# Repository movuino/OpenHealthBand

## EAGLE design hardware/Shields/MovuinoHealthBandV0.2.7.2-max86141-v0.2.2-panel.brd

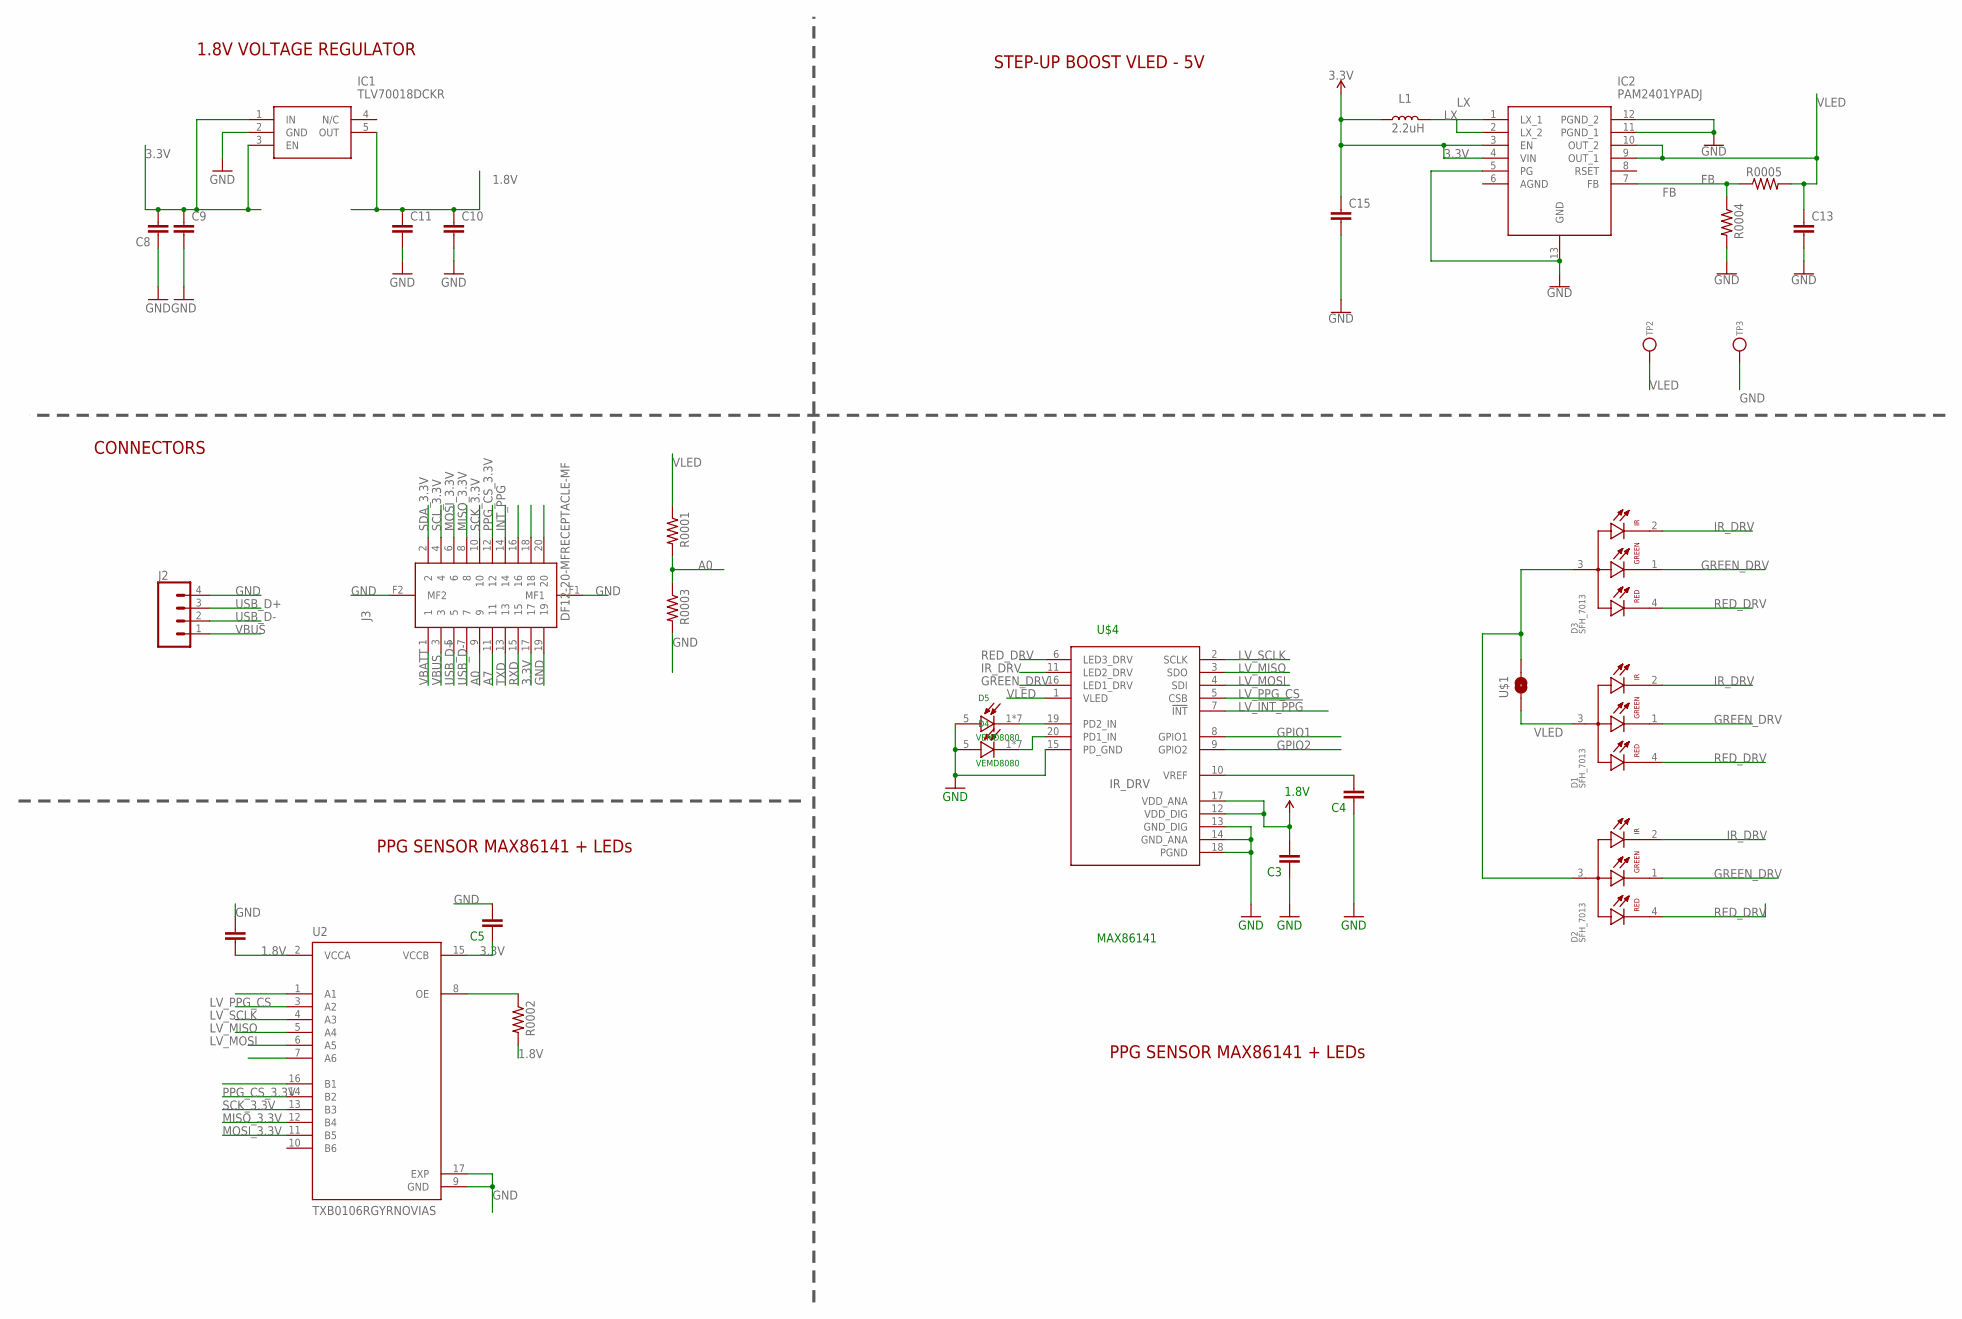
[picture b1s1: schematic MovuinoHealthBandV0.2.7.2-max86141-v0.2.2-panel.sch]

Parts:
C3: 1uF; 0402-CAP
C4: 10uF; 0402-CAP
C5, C6: 0.1uF; 0402-CAP
C8, C15: 10uF; 0402-CAP-SMALL-TDOCU
C9, C10: 0.1uF; 0402-CAP-SMALL-TDOCU
C11: 4.7uF; 0402-CAP-SMALL-TDOCU
C13: 22uF; 0402-CAP-SMALL-TDOCU
D1, D2, D3: SFH_7013
D4, D5: VEMD8080; XDCR_VEMD8080
IC1: TLV70018DCKR; SOT65P210X110-5N
IC2: PAM2401YPADJ; SON45P295X295X60-13N
J2: CONN_04POGO-2.54; POGO_2.54_X4
J3: DF12-20-MFRECEPTACLE-MF; DF12-20-DS
L1: 2.2uH; INDC2016X100N
R0001, R0002, R0003, R0004: 100K; 0402-RES
R0005: 750K; 0402-RES
TP2, TP3: TESTPOINT1MM-ROUND-CREAM; TESTPOINT_ROUND_1MM-CREAM
U2: TXB0106RGYRNOVIAS; QFN50P400X350X100-17N-2
U$1: 0402-JUMPER
U$4: MAX86141; 20_PIN_WLP

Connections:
1.8V: C3.2, C6.1, C10.1, C11.1, IC1.5 (OUT), R0002.2, U2.2 (VCCA), U$4.12 (VDD_DIG), U$4.17 (VDD_ANA)
3.3V: C5.1, C8.2, C9.1, C15.1, IC1.1 (IN), IC1.3 (EN), IC2.3 (EN), IC2.4 (VIN), J3.17, L1.1, U2.15 (VCCB)
A0: J3.9, R0001.2, R0003.1
A7: J3.11
FB: IC2.7 (FB), R0004.1, R0005.1
GND: C3.1, C4.1, C5.2, C6.2, C8.1, C9.2, C10.2, C11.2, C13.2, C15.2, D4.5 (A), D5.5 (A), IC1.2 (GND), IC2.5 (PG), IC2.11 (PGND_1), IC2.12 (PGND_2), IC2.13 (GND), J2.4, J3.19, J3.F1 (MF1), J3.F2 (MF2), R0003.2, R0004.2, TP3.P$1, U2.9 (GND), U2.17 (EXP), U$4.13 (GND_DIG), U$4.14 (GND_ANA), U$4.15 (PD_GND), U$4.18 (PGND)
GPIO1: U$4.8 (GPIO1)
GPIO2: U$4.9 (GPIO2)
GREEN_DRV: D1.1 (CATHODE_EMITTER_2), D2.1 (CATHODE_EMITTER_2), D3.1 (CATHODE_EMITTER_2), U$4.16 (LED1_DRV)
INT_PPG: J3.14
IR_DRV: D1.2 (CATHODE_EMITTER_3), D2.2 (CATHODE_EMITTER_3), D3.2 (CATHODE_EMITTER_3), U$4.11 (LED2_DRV)
LV_!INT_PPG!: U$4.7 (!INT!)
LV_MISO: U2.5 (A4), U$4.3 (SDO)
LV_MOSI: U2.6 (A5), U$4.4 (SDI)
LV_PPG_CS: U2.3 (A2), U$4.5 (CSB)
LV_SCLK: U2.4 (A3), U$4.2 (SCLK)
LX: IC2.1 (LX_1), IC2.2 (LX_2), L1.2
MISO_3.3V: J3.8, U2.12 (B4)
MOSI_3.3V: J3.6, U2.11 (B5)
unnamed: R0002.1, U2.8 (OE)
unnamed: C4.2, U$4.10 (VREF)
unnamed: D5.1 (C), D5.2 (C), D5.3 (C), D5.4 (C), D5.6 (C), D5.7 (C), D5.8 (C), U$4.19 (PD2_IN)
unnamed: D4.1 (C), D4.2 (C), D4.3 (C), D4.4 (C), D4.6 (C), D4.7 (C), D4.8 (C), U$4.20 (PD1_IN)
unnamed: D2.3 (ANODE_EMITTER_1/2/3), D3.3 (ANODE_EMITTER_1/2/3), U$1.2
PPG_CS_3.3V: J3.12, U2.14 (B2)
RED_DRV: D1.4 (CATHODE_EMITTER_1), D2.4 (CATHODE_EMITTER_1), D3.4 (CATHODE_EMITTER_1), U$4.6 (LED3_DRV)
RXD: J3.15
SCK_3.3V: J3.10, U2.13 (B3)
SCL_3.3V: J3.4
SDA_3.3V: J3.2
TXD: J3.13
USB_D+: J2.3, J3.5
USB_D-: J2.2, J3.7
VBATT: J3.1
VBUS: J2.1, J3.3
VLED: C13.1, D1.3 (ANODE_EMITTER_1/2/3), IC2.9 (OUT_1), IC2.10 (OUT_2), R0001.1, R0005.2, TP2.P$1, U$1.1, U$4.1 (VLED)

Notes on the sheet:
PPG SENSOR MAX86141 + LEDs
STEP-UP BOOST VLED - 5V
1.8V VOLTAGE REGULATOR
CONNECTORS

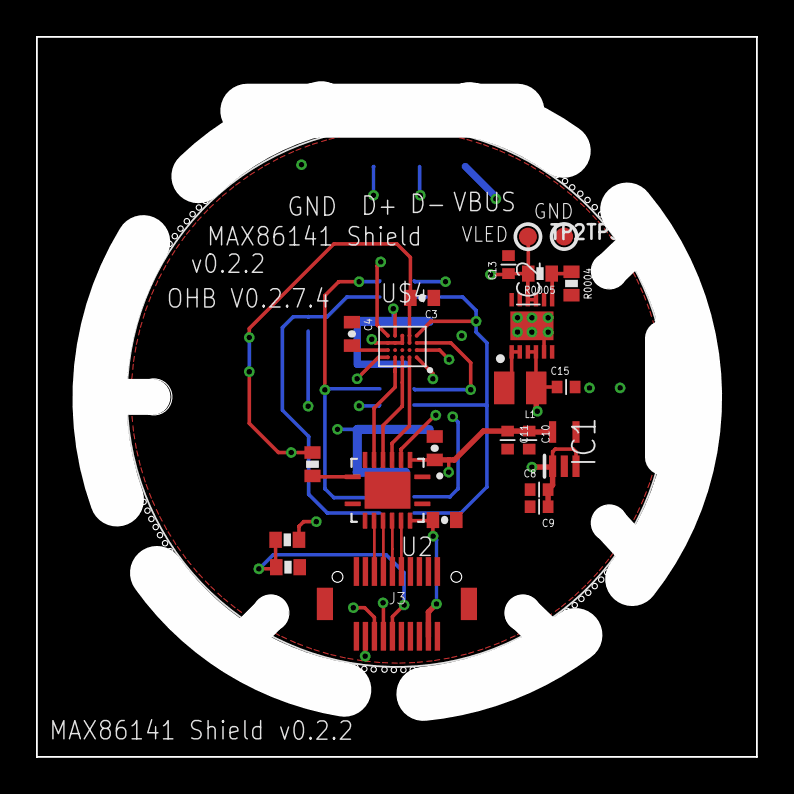
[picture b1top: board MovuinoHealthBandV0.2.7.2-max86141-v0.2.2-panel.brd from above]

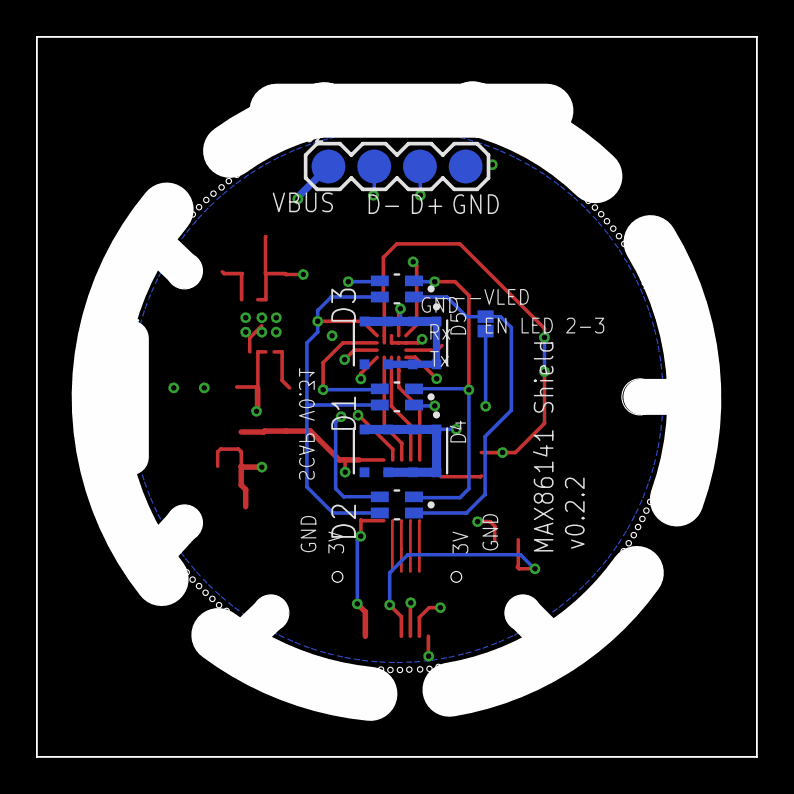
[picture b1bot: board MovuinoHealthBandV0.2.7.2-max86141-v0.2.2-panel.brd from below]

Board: 4 copper layers, 40.0 x 40.0 mm, 30 parts (7 on the bottom side), 26 nets.

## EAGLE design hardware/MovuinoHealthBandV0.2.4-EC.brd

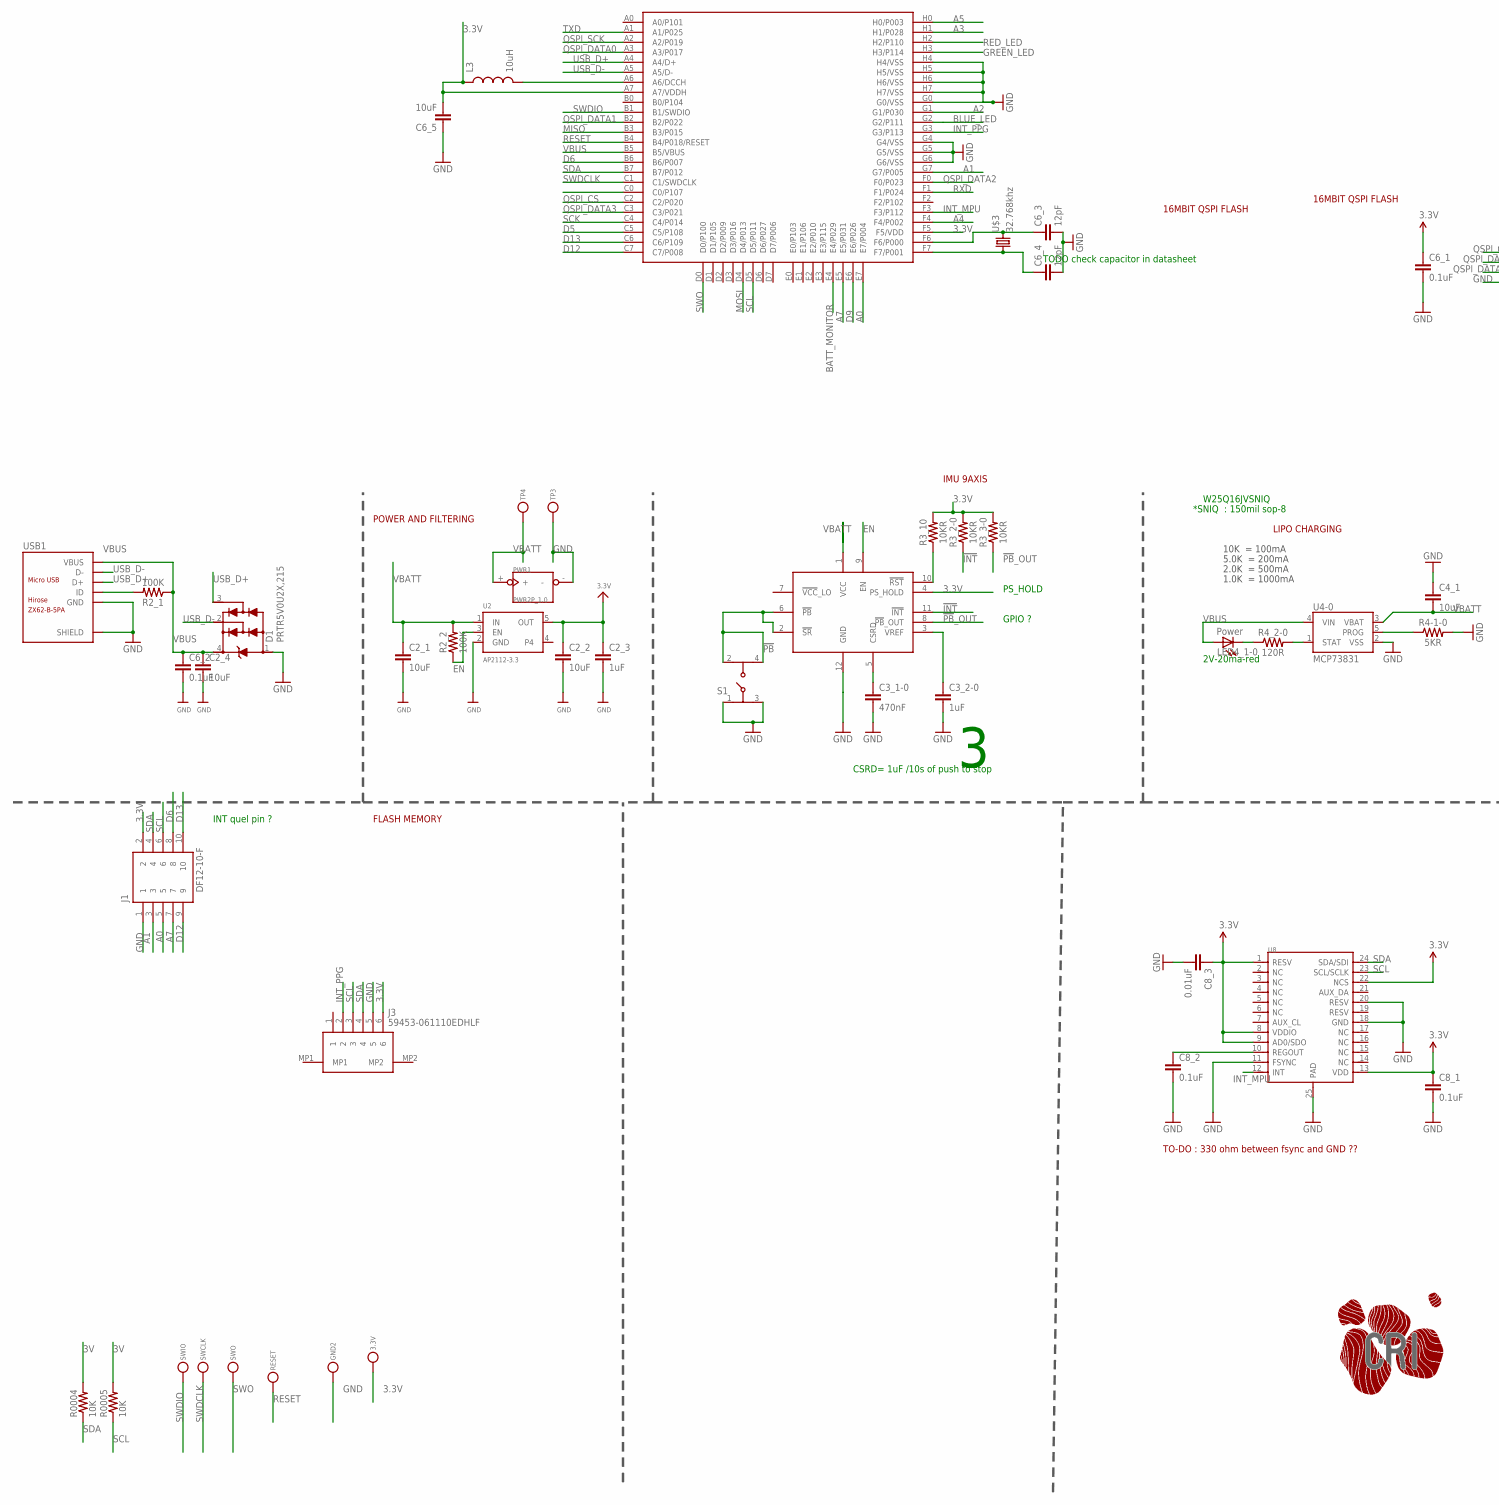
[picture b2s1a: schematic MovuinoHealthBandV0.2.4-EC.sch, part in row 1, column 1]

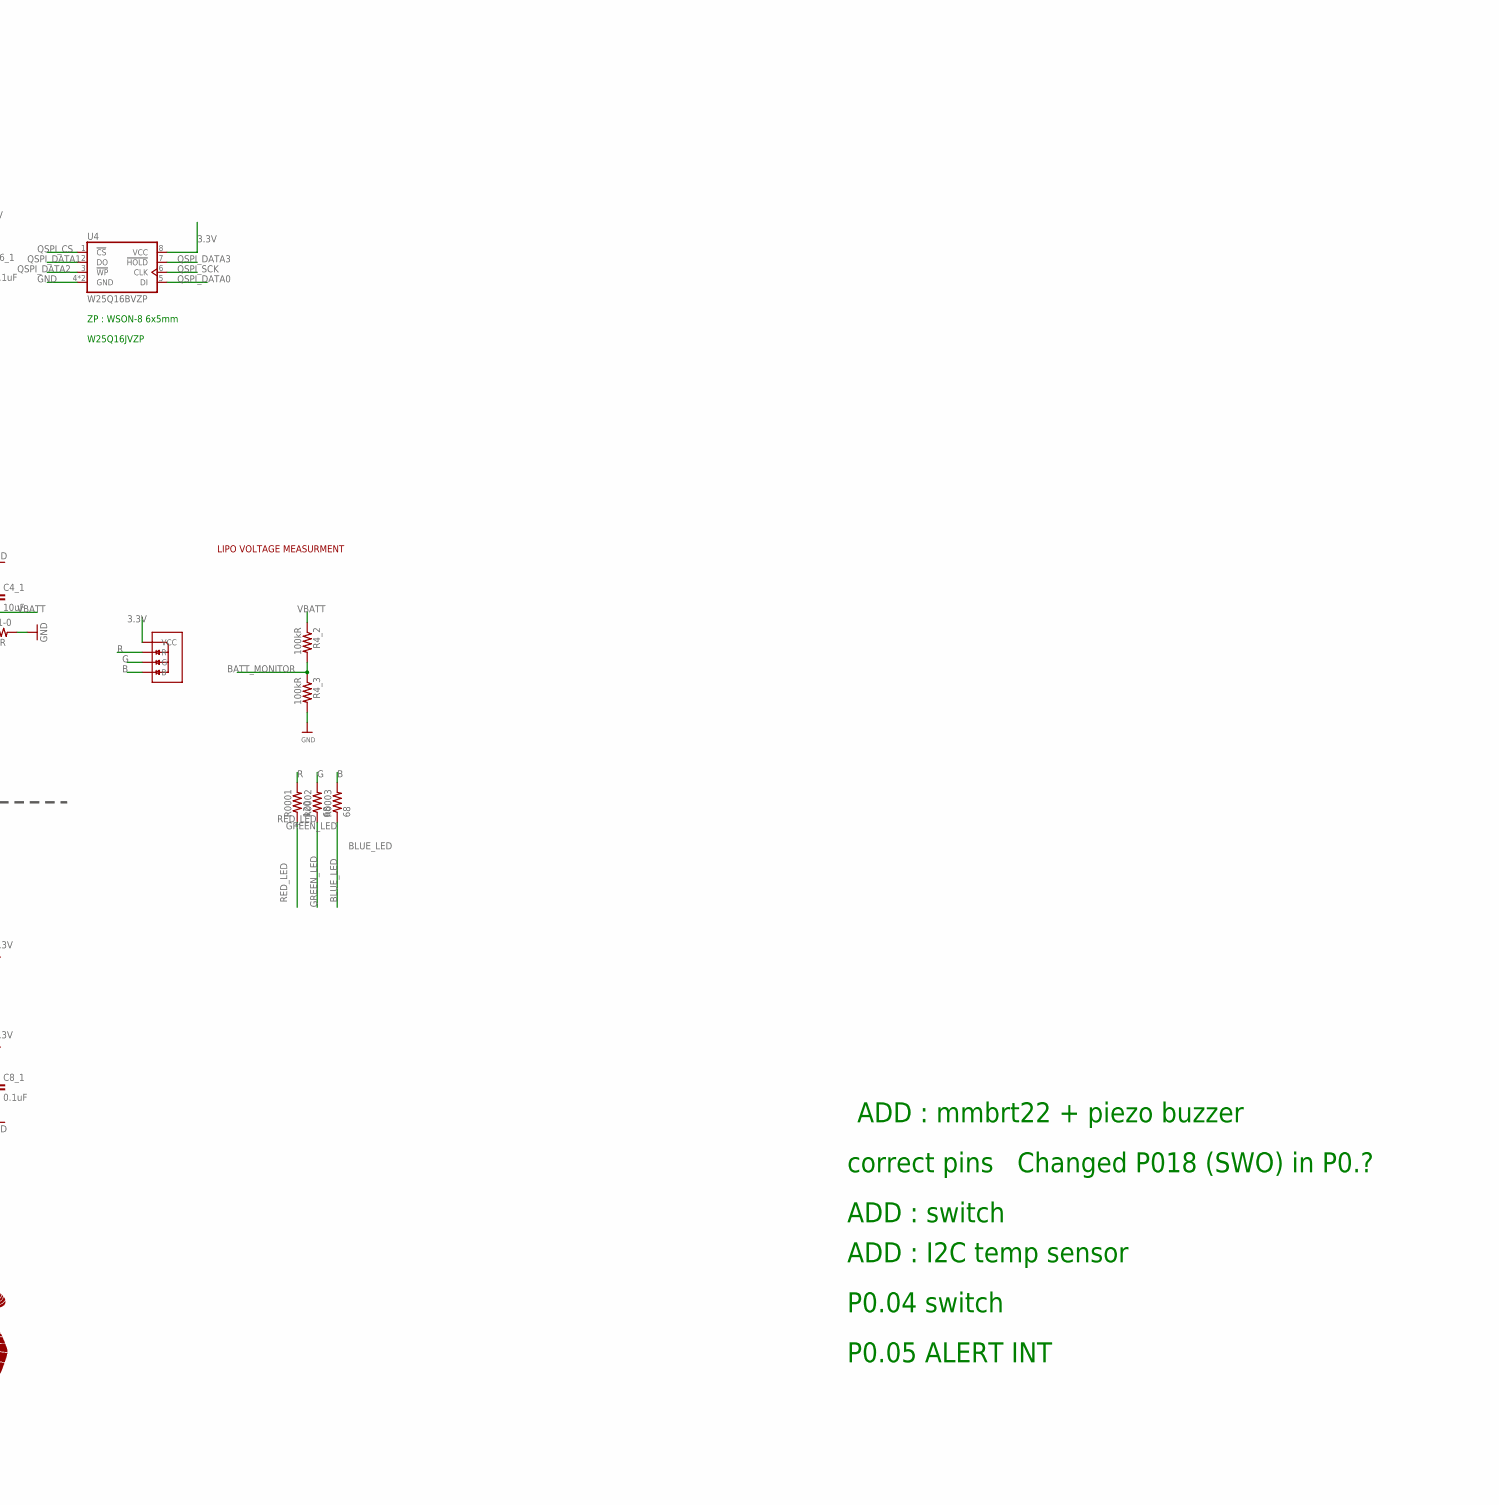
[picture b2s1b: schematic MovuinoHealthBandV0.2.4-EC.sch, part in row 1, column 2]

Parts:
3.3V: TESTPOINTROUND1MM; TESTPOINT_ROUND_1MM
C2_1, C2_2, C2_4, C4_1, C6_5: 10uF; 0402-CAP-SMALL-TDOCU
C2_3: 1uF; 0402-CAP-SMALL-TDOCU
C3_1-0: 470nF; 0402-CAP
C3_2-0: 1uF; 0402-CAP
C6_1, C6_2, C8_1, C8_2: 0.1uF; 0402-CAP-SMALL-TDOCU
C6_3, C6_4: 12pF; 0402-CAP-SMALL-TDOCU
C8_3: 0.01uF; 0402-CAP-SMALL-TDOCU
D1: PRTR5V0U2X,215; SOT143B
GND2: TESTPOINTROUND1MM; TESTPOINT_ROUND_1MM
J1: DF12-10-F; DF12-10-DP
J3: 59453-061110EDHLF; 59453061110EDHLF
L3: 10uH; C0402
LED4_1-0: Power; LED-0603
PWR1: PWR2P_1.0
R0001: 120; 0402-RES
R0002, R0003: 68; 0402-RES
R2_1, R2_2: 100K; R0402-SMALL-TDOCU
R3_2-0, R3_3-0, R3_10: 10KR; R0402-SMALL-TDOCU
R0004, R0005: 10K; 0402-RES
R4-1-0: 5KR; R0402-SMALL-TDOCU
R4_2, R4_3: 100kR; 0402-RES
R4_2-0: 120R; R0402-SMALL-TDOCU
RESET: TESTPOINTROUND1MM; TESTPOINT_ROUND_1MM
S1: 434331045822
SWCLK: TESTPOINTROUND1MM; TESTPOINT_ROUND_1MM
SWIO: TESTPOINTROUND1MM; TESTPOINT_ROUND_1MM
SWO: TESTPOINTROUND1MM; TESTPOINT_ROUND_1MM
TP3, TP4: TESTPOINT1X1.5MM_NOCREAM_NOSILK; PAD-1X1.5_NOSILK
U2: AP2112-3.3; SOT23-5
U3: BC840
U3-0: STM6601; TDFN12
U4: W25Q16BVZP; WSON8
U4-0: MCP73831; SOT23-5
U8: MPU-9250; LEAD-QFN24
U$2: LOGO-CRI-NEW-110MM-BOTTOM-SILK; LOGO_CRI-NEW-BMP10MM-BOTTOM
U$3: 32.768khz; CRYSTAL-SMD-2X1.2-ABS06
U$24: LRTB_R48G
USB1: MICRO-USB-SMD(ZX62-B-5PA)TB1; MICRO-USB5+6P-SMD-0.65-AB-TB

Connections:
3.3V: 3.3V.P$1, C2_2.1, C2_3.1, C6_1.1, C6_5.2, C8_1.1, C8_3.1, J1.2, J3.6, L3.1, R3_2-0.2, R3_3-0.2, R3_10.2, U2.5 (OUT), U3.A7 (A7/VDDH), U3.F5 (F5/VDD), U3-0.4 (PS_HOLD), U4.8 (VCC), U8.1 (RESV), U8.8 (VDDIO), U8.9 (AD0/SDO), U8.13 (VDD), U8.22 (NCS), U$24.1 (VCC)
3V: R0004.2, R0005.2
!INT!: R3_2-0.1, U3-0.11 (!INT!)
!PB!: S1.2 (4), S1.4 (2), U3-0.2 (!SR!), U3-0.6 (!PB!)
!PB!_OUT: R3_3-0.1, U3-0.8 (!PB!_OUT)
A0: J1.5, U3.E7 (E7/P004)
A1: J1.3, U3.G7 (G7/P005)
A2: U3.G1 (G1/P030)
A3: U3.H1 (H1/P028)
A4: U3.F4 (F4/P002)
A5: U3.H0 (H0/P003)
A7: J1.7, U3.E5 (E5/P031)
B: R0003.2, U$24.4 (B)
BATT_MONITOR: R4_2.2, R4_3.1, U3.E4 (E4/P029)
BLUE_LED: R0003.1, U3.G2 (G2/P111)
CSRD: C3_1-0.1, U3-0.5 (CSRD)
D5: U3.C5 (C5/P108)
D6: J1.8, U3.B6 (B6/P007)
D9: U3.E6 (E6/P026)
D12: J1.9, U3.C7 (C7/P008)
D13: J1.10, U3.C6 (C6/P109)
EN: R2_2.1, U2.3 (EN), U3-0.9 (EN)
G: R0002.2, U$24.3 (G)
GND: C2_1.2, C2_2.2, C2_3.2, C2_4.2, C3_1-0.2, C3_2-0.2, C4_1.1, C6_1.2, C6_2.2, C6_3.2, C6_4.2, C6_5.1, C8_1.2, C8_2.2, C8_3.2, D1.1, GND2.P$1, J1.1, J3.5, PWR1.-, R4-1-0.2, R4_3.2, S1.1 (3), S1.3 (1), TP3.P$1, U2.2 (GND), U3.G0 (G0/VSS), U3.G4 (G4/VSS), U3.G5 (G5/VSS), U3.G6 (G6/VSS), U3.H4 (H4/VSS), U3.H5 (H5/VSS), U3.H6 (H6/VSS), U3.H7 (H7/VSS), U3-0.12 (GND), U4.4 (GND), U4.9 (GND), U4-0.2 (VSS), U8.11 (FSYNC), U8.18 (GND), U8.20 (RESV), U8.25 (PAD), USB1.5 (GND), USB1.P1 (SHIELD), USB1.P2 (SHIELD), USB1.P5 (SHIELD), USB1.P6 (SHIELD), USB1.P$3 (SHIELD), USB1.P$4 (SHIELD)
GREEN_LED: R0002.1, U3.H3 (H3/P114)
INT_MPU: U3.F3 (F3/P112), U8.12 (INT)
INT_PPG: J3.2, U3.G3 (G3/P113)
MISO: U3.B3 (B3/P015)
MOSI: U3.D4 (D4/P013)
unnamed: R4_2-0.2, U4-0.1 (STAT)
unnamed: R2_1.2, USB1.4 (ID)
unnamed: C6_3.1, U3.F6 (F6/P000), U$3.P$2 (2)
unnamed: C6_4.1, U3.F7 (F7/P001), U$3.P$1 (1)
unnamed: R3_10.1, U3-0.10 (!RST!)
unnamed: LED4_1-0.C, R4_2-0.1
unnamed: R4-1-0.1, U4-0.5 (PROG)
unnamed: L3.2, U3.A6 (A6/DCCH)
unnamed: C8_2.1, U8.10 (REGOUT)
QSPI_CS: U3.C2 (C2/P020), U4.1 (!CS!)
QSPI_DATA0: U3.A3 (A3/P017), U4.5 (DI)
QSPI_DATA1: U3.B2 (B2/P022), U4.2 (DO)
QSPI_DATA2: U3.F0 (F0/P023), U4.3 (!WP!)
QSPI_DATA3: U3.C3 (C3/P021), U4.7 (!HOLD!)
QSPI_SCK: U3.A2 (A2/P019), U4.6 (CLK)
R: R0001.2, U$24.2 (R)
RED_LED: R0001.1, U3.H2 (H2/P110)
RESET: RESET.P$1, U3.B4 (B4/P018/RESET)
RXD: U3.F1 (F1/P024)
SCK: U3.C4 (C4/P014)
SCL: J1.6, J3.3, R0005.1, U3.D5 (D5/P011), U8.23 (SCL/SCLK)
SDA: J1.4, J3.4, R0004.1, U3.B7 (B7/P012), U8.24 (SDA/SDI)
SWDCLK: SWCLK.P$1, U3.C1 (C1/SWDCLK)
SWDIO: SWIO.P$1, U3.B1 (B1/SWDIO)
SWO: SWO.P$1, U3.D0 (D0/P100)
TXD: U3.A1 (A1/P025)
USB_D+: D1.3, U3.A4 (A4/D+), USB1.3 (D+)
USB_D-: D1.2, U3.A5 (A5/D-), USB1.2 (D-)
VBATT: C2_1.1, C4_1.2, PWR1.+, R2_2.2, R4_2.1, TP4.P$1, U2.1 (IN), U3-0.1 (VCC), U4-0.3 (VBAT)
VBUS: C2_4.1, C6_2.1, D1.4, LED4_1-0.A, R2_1.1, U3.B5 (B5/VBUS), U4-0.4 (VIN), USB1.1 (VBUS)
VREF: C3_2-0.1, U3-0.3 (VREF)

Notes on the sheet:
LIPO VOLTAGE MEASURMENT
ADD : mmbrt22 + piezo buzzer
correct pins
ADD : switch
ADD : I2C temp sensor
Changed P018 (SWO) in P0.?
P0.04 switch
P0.05 ALERT INT
TO-DO : 330 ohm between fsync and GND ??
IMU 9AXIS
POWER AND FILTERING
CSRD= 1uF /10s of push to stop
10K = 100mA
5.0K = 200mA
2.0K = 500mA
1.0K = 1000mA
LIPO CHARGING
2V-20ma-red
FLASH MEMORY
16MBIT QSPI FLASH
W25Q16JVSNIQ
*SNIQ : 150mil sop-8
TODO check capacitor in datasheet
ZP : WSON-8 6x5mm
W25Q16JVZP
PS_HOLD
GPIO ?
INT quel pin ?

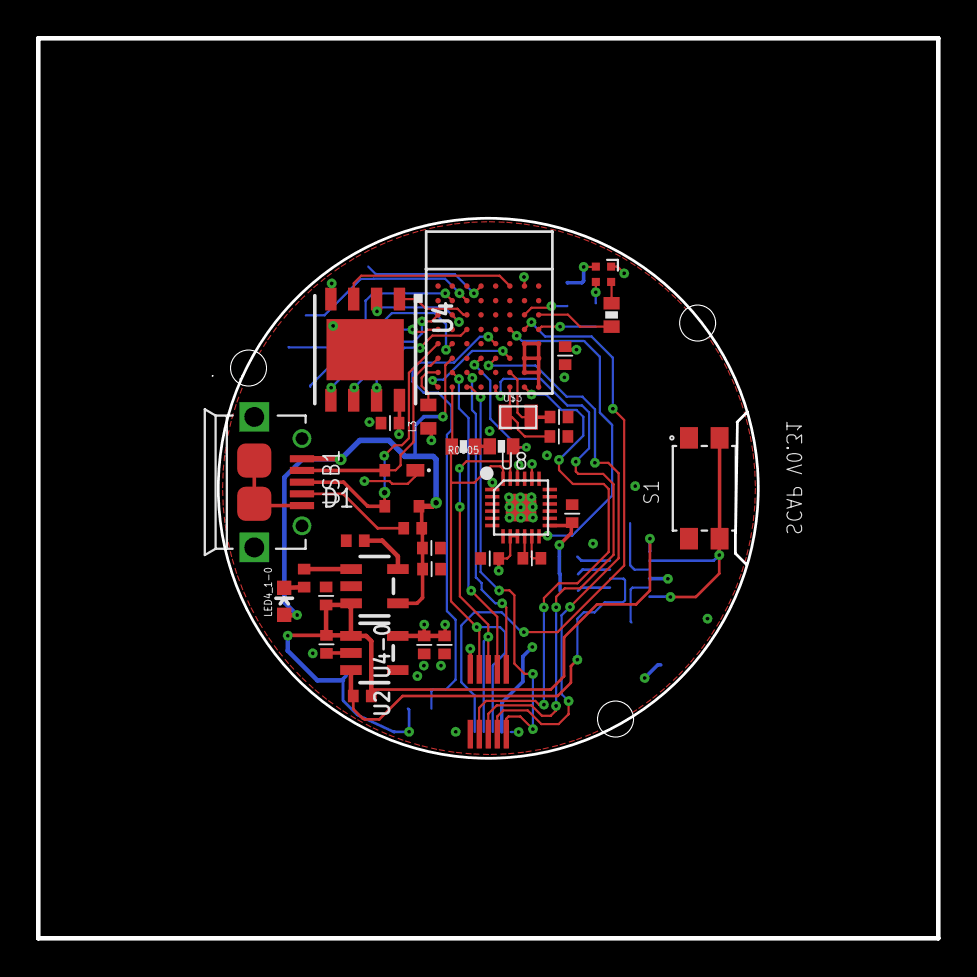
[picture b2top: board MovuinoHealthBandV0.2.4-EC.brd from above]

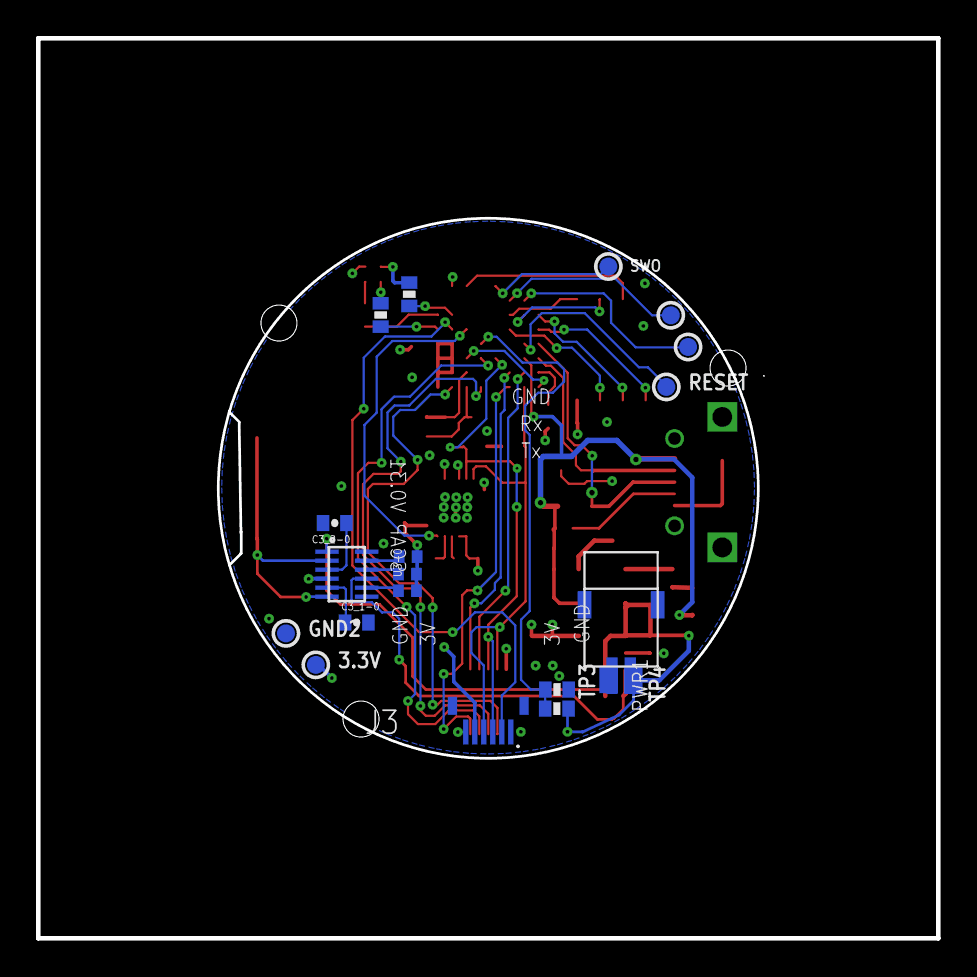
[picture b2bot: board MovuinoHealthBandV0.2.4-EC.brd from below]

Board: 4 copper layers, 50.0 x 50.0 mm, 54 parts (20 on the bottom side), 49 nets.

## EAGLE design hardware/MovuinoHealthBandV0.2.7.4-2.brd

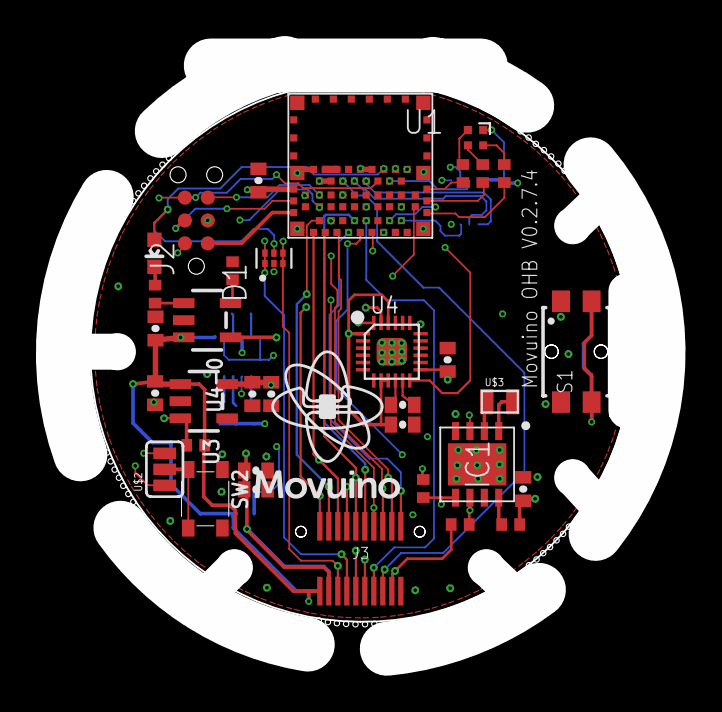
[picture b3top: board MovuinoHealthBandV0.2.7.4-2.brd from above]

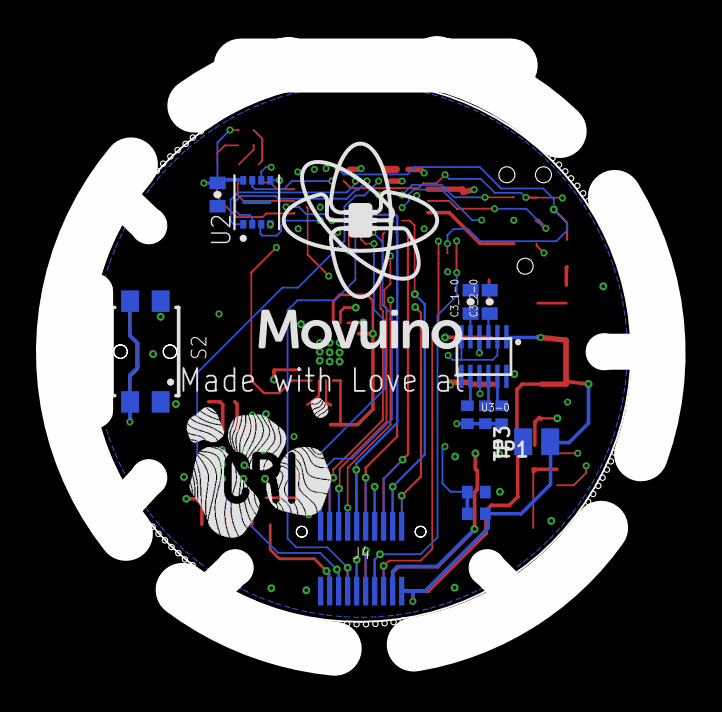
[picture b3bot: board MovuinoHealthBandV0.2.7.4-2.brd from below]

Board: 4 copper layers, 29.5 x 30.0 mm, 51 parts (14 on the bottom side), 55 nets.

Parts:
C2_1, C2_2, C2_4, C4_1, C6_5, C8_1: 10uF; 0402-CAP
C2_3, C6_1, C8_6, C8_7: 0.1uF; 0402-CAP
C2_5, C3_2-0: 1uF; 0402-CAP
C3_1-0: 470nF; 0402-CAP
C8_5: 0.01uF; 0402-CAP
D1: PRTR5V0U2X,215PRTR5V0U2F; SOT-886
IC1: PCF8523TK_1,118; SON80P400X400X100-9N
J2: TC2030-MCP-NL
J3: DF12-20RECEPTACLE_NO-MF; DF12-20-DS-NO_MF
J4: DF12-20HEADER-5MM_NO-MF; DF12-20-DP-NL-(5.0)
LED4_1-0: Power; LED-0603
R0001, R2_3: 100kR; R0402-SMALL-TDOCU
R0002, R4_2-0: 120R; R0402-SMALL-TDOCU
R0003, R0004: 68; R0402-SMALL-TDOCU
R4_1-0: 5KR; R0402-SMALL-TDOCU
R0005: 100KR; R0402-SMALL-TDOCU
R0006, R0007, R0008, R0009, R0010: 10kR; R0402-SMALL-TDOCU
R0011: 1kR; R0402-SMALL-TDOCU
S1, S2: 4363X10458XX
SW2: BTN_KMT0
TP1, TP3: PAD-1X1.5_NOSILK
U1: ISP1807-LRISP1807-LR_ISP1807-LR; ISP1807-LR
U2: GD25Q16CEIGR; USON8-2X3
U3: AP2112K-3.3TRG13.3V; SOT23-5
U3-0: STM6601; TDFN12
U4: LEAD-QFN24-OLD
U4-0: MCP73831; SOT23-5
U$2: 0402-JUMPER3; SJ_3
U$3: 32.768khz; CRYSTAL-SMD-2X1.2-ABS06
U$5: LRTB_R48G
U$7: LOGO_MOVUINOTOP; LOGO_MOVUINO_BMP_10MM
U$8: LOGO_MOVUINOBOTTOM_11MM; LOGO_MOVUINO_BMP_11MM-BOTTOM
U$9: LOGO-CRI-NEW-110MM-BOTTOM-SILK; LOGO_CRI-NEW-BMP10MM-BOTTOM

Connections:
3.3V: C2_2.1, C2_3.1, C6_1.1, C6_5.2, C8_1.1, C8_5.1, C8_6.1, J2.2, J3.17, J4.3, R0006.2, R0007.2, R0008.2, R0009.2, R0010.2, R0011.1, U1.26, U2.8, U3.5, U3-0.4, U4.1, U4.8, U4.9, U4.13, U4.22, U$5.1
!INT!: R0007.1, U3-0.11
!PB!: S1.2, S1.4, S2.2, S2.4, U3-0.2, U3-0.6
!PB!_OUT: R0006.1, U3-0.8
A0: J3.9, J4.11, U1.42
A2: J3.16, J4.6, U1.35
A3: J3.18, J4.4, U1.36
A5: J3.20, J4.2, U1.38
A7: J3.11, J4.9, U1.44
B: R0004.2, U$5.4
BATT_MONITOR: R0001.1, R0005.2, U1.40
BLUE_LED: R0004.1, U1.6
CSRD: C3_1-0.1, U3-0.5
CS_3.3V: J3.12, J4.10, U1.39
DFU: U1.49, U$2.3
EN: R2_3.1, U3.3, U3-0.9
G: R0003.2, U$5.3
GND: C2_1.2, C2_2.2, C2_3.2, C2_4.2, C2_5.2, C3_1-0.2, C3_2-0.2, C4_1.1, C6_1.2, C6_5.1, C8_1.2, C8_5.2, C8_6.2, C8_7.2, D1.2, IC1.4, IC1.9, J2.3, J3.19, J4.1, R4_1-0.1, R0005.1, S1.1, S1.3, S2.1, S2.3, SW2.A, SW2.A', TP3.P$1, U1.1, U1.7, U1.14, U1.16, U1.18, U1.21, U1.23, U1.24, U1.25, U1.31, U2.4, U3.2, U3-0.12, U4.11, U4.18, U4.20, U4.25, U4-0.2
GREEN_LED: R0003.1, U1.4
INT_MPU: U1.59, U4.12
INT_PPG: J3.14, J4.8, U1.53
MISO_3.3V: J3.8, J4.14, U1.56
MOSI_3.3V: J3.6, J4.16, U1.32
unnamed: R4_2-0.1, U4-0.1
unnamed: IC1.2, U$3.P$1
unnamed: U1.20, U1.22
unnamed: IC1.1, U$3.P$2
unnamed: R0008.1, U3-0.10
unnamed: LED4_1-0.C, R4_2-0.2
unnamed: R4_1-0.2, U4-0.5
unnamed: IC1.8, R0011.2
unnamed: C8_7.1, U4.10
QSPI_CS: U1.15, U2.1
QSPI_DATA0: U1.27, U2.5
QSPI_DATA1: U1.17, U2.2
QSPI_DATA2: U1.47, U2.3
QSPI_DATA3: U1.11, U2.7
QSPI_SCK: U1.45, U2.6
R: R0002.2, U$5.2
RED_LED: R0002.1, U1.2
RESET: J2.6, U1.13, U$2.1
RXD: J3.15, J4.5, U1.19
SCK_3.3V: J3.10, J4.12, U1.34
SCL_3.3V: IC1.6, J3.4, J4.18, R0010.1, U1.33, U4.23
SDA_3.3V: IC1.5, J3.2, J4.20, R0009.1, U1.3, U4.24
SWDCLK: J2.1, U1.30
SWDIO: J2.4, U1.28
SWITCH: SW2.B, SW2.B', U$2.2
SWO: J2.5, U1.57
TXD: J3.13, J4.7, U1.41
USB_D+: D1.3, D1.4, J3.5, J4.15, U1.8
USB_D-: D1.1, D1.6, J3.7, J4.13, U1.10
VBATT: C2_1.1, C4_1.2, IC1.3, J3.1, J4.19, R0001.2, R2_3.2, TP1.P$1, U3.1, U3-0.1, U4-0.3
VBUS: C2_4.1, C2_5.1, D1.5, J3.3, J4.17, LED4_1-0.A, U1.12, U4-0.4
VREF: C3_2-0.1, U3-0.3

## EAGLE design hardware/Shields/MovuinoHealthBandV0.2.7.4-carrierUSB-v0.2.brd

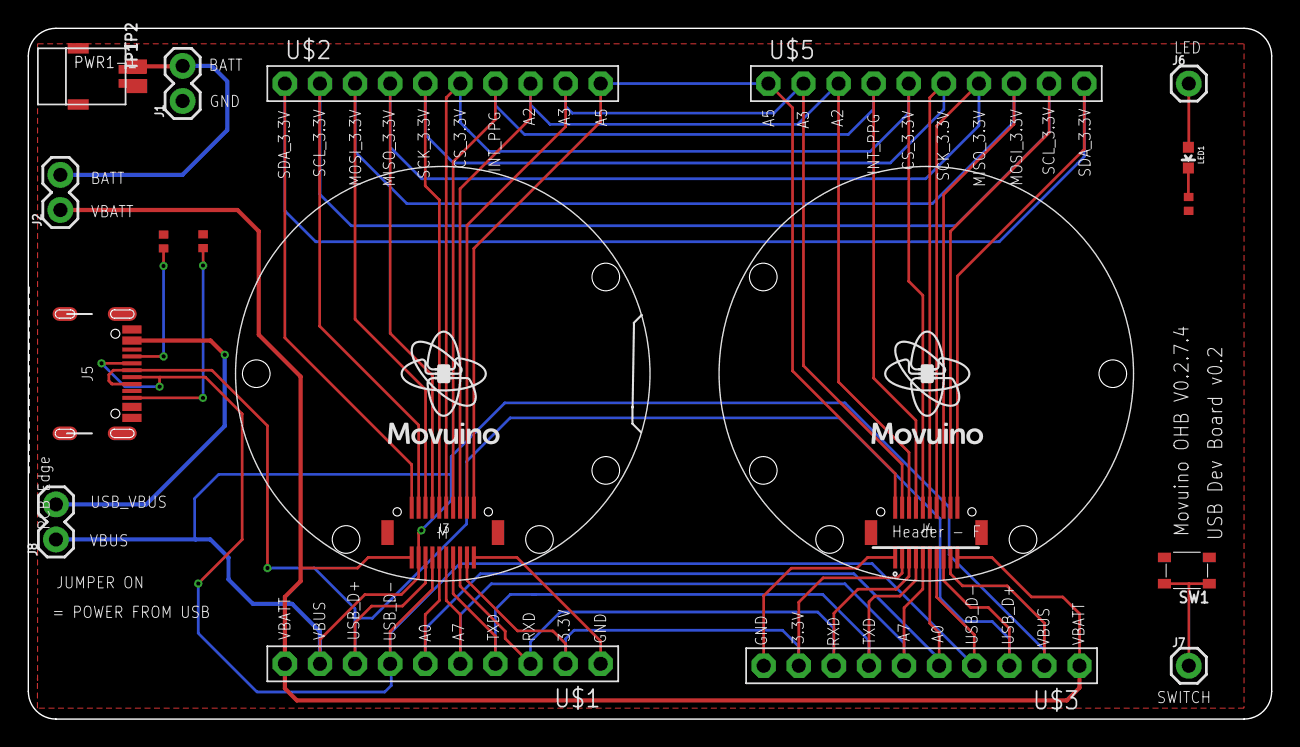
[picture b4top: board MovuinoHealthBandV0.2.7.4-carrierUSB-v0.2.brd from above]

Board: 2 copper layers, 90.0 x 50.0 mm, 23 parts (0 on the bottom side), 27 nets.

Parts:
J1, J2, J8: 1X02
J3: DF12-20-MFRECEPTACLE-MF; DF12-20-DS
J4: DF12-20-MFHEADER-5MM-LEGS-BOSS; DF12(5.0)-20-DP
J5: USB-C-16P
J6, J7: 1X01
LED1: LED-0603
PWR1-1: PWR2P_1.0
R2_1: 120; R0402-SMALL-TDOCU
R2_3, R2_4: 5.1K; R0402-SMALL-TDOCU
SW1: BTN_KMT0
TP1, TP2: PAD-1X1.5_NOSILK
U$1, U$2, U$3, U$5: PINHD-1X10; 1X10-BIG
U$7, U$8: LOGO_MOVUINOTOP; LOGO_MOVUINO_BMP_10MM
U$9: LOGO-CRI-NEW-110MM-BOTTOM-SILK; LOGO_CRI-NEW-BMP10MM-BOTTOM

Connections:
3.3V: J3.17, J4.3, U$1.2, U$3.9
A0: J3.9, J4.11, U$1.6, U$3.5
A2: J3.16, J4.6, U$2.8, U$5.3
A3: J3.18, J4.4, U$2.9, U$5.2
A5: J3.20, J4.2, U$2.10, U$5.1
A7: J3.11, J4.9, U$1.5, U$3.6
BATT: J1.2, J2.2, PWR1-1.+, TP2.P$1
CS_3.3V: J3.12, J4.10, U$2.6, U$5.5
GND: J1.1, J3.19, J3.F1, J3.F2, J4.1, J4.F1, J4.F2, J5.A1B12, J5.SHLD1, J5.SHLD2, J5.SHLD3, J5.SHLD4, J5.SHLD5, J5.SHLD6, J5.SHLD7, J5.SHLD8, PWR1-1.-, R2_1.1, R2_3.1, R2_4.1, SW1.B, SW1.B', TP1.P$1, U$1.1, U$3.10
INT_PPG: J3.14, J4.8, U$2.7, U$5.4
MISO_3.3V: J3.8, J4.14, U$2.4, U$5.7
MOSI_3.3V: J3.6, J4.16, U$2.3, U$5.8
unnamed: LED1.C, R2_1.2
unnamed: J6.1, LED1.A
unnamed: J7.1, SW1.A, SW1.A'
unnamed: J5.A5, R2_4.2
unnamed: J5.B5, R2_3.2
RXD: J3.15, J4.5, U$1.3, U$3.8
SCK_3.3V: J3.10, J4.12, U$2.5, U$5.6
SCL_3.3V: J3.4, J4.18, U$2.2, U$5.9
SDA_3.3V: J3.2, J4.20, U$2.1, U$5.10
TXD: J3.13, J4.7, U$1.4, U$3.7
USB_D+: J3.5, J4.15, J5.A6, J5.B6, U$1.8, U$3.3
USB_D-: J3.7, J4.13, J5.A7, J5.B7, U$1.7, U$3.4
USB_VBUS: J5.A4B9, J8.2
VBATT: J2.1, J3.1, J4.19, U$1.10, U$3.1
VBUS: J3.3, J4.17, J8.1, U$1.9, U$3.2

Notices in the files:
parts and their libraries:
microbuilder: This work is placed in the public domain, and may be freely used for commercial and non-commercial work with the following conditions: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
Wurth_Elektronik_Electromechanic_Switch_: Copyright: Würth Elektronik
